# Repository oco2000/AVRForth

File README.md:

# AVRForth
Forth language compiler for AVR microcontrollers

The documentation is in [here](manual/manual.en.md)!

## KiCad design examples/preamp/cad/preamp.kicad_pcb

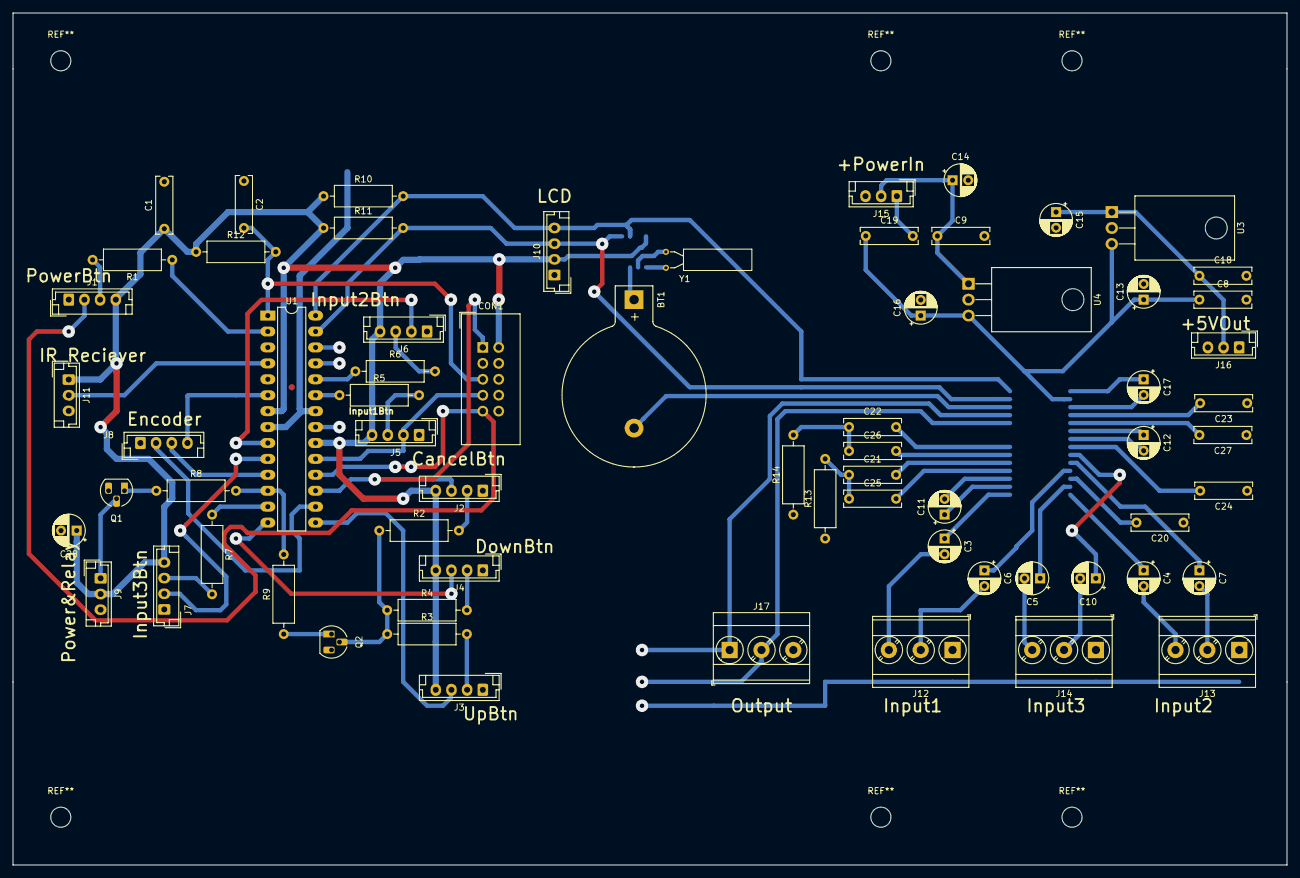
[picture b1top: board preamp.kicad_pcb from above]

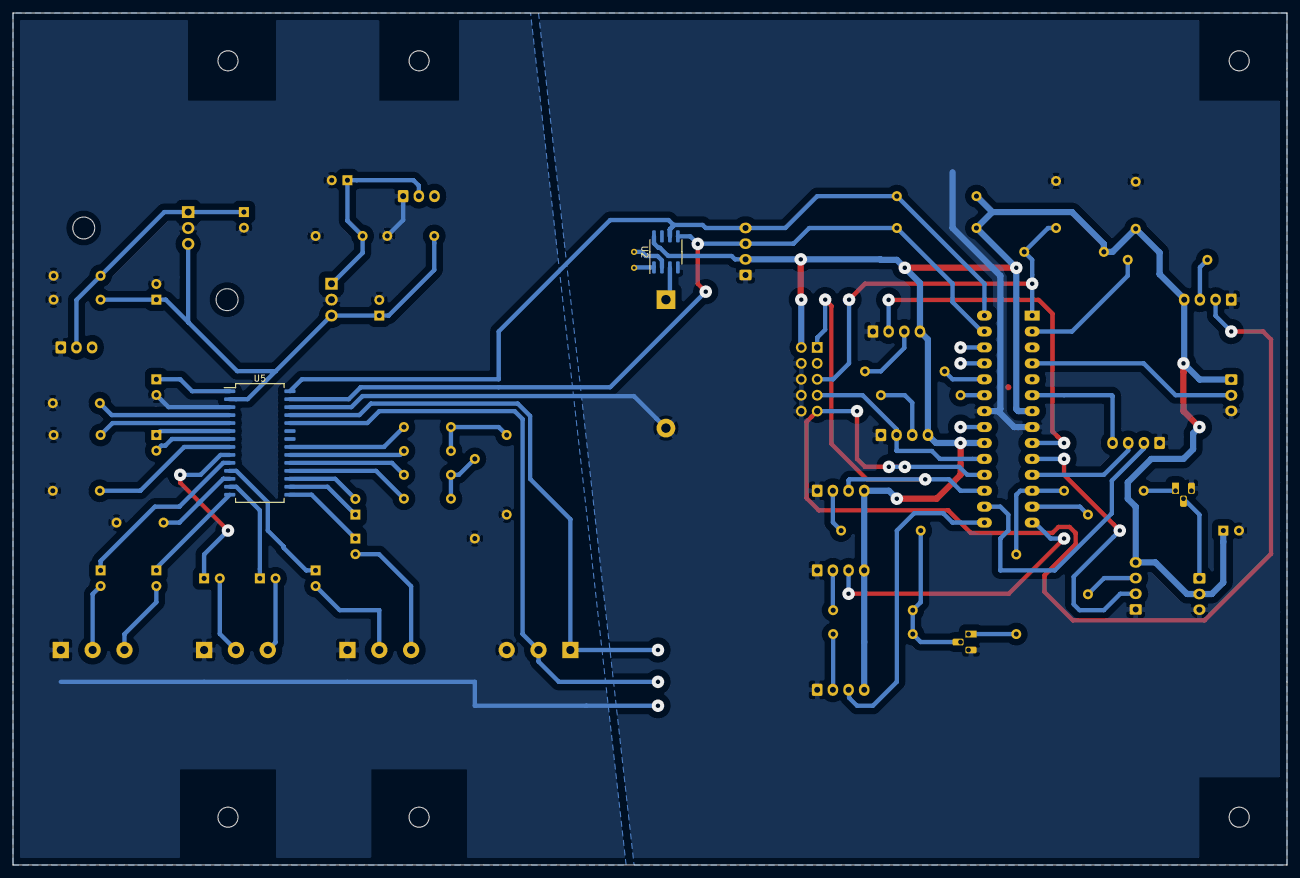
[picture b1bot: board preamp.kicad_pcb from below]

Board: 2 copper layers, 203.2 x 135.9 mm, 69 parts (2 on the bottom side), 68 nets.

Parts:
BT1: Battery_Cell; BatteryHolder_Keystone_103_1x20mm
C1, C2, C18, C19, C20, C21, C22, C24, C25, C26: 100nF; C_Rect_L9.0mm_W2.5mm_P7.50mm_MKT
C3, C4, C5, C6, C7, C10, C11, C12, C17: 2.2uF; CP_Radial_D5.0mm_P2.50mm
C8, C9: 0.33uF; C_Rect_L9.0mm_W2.5mm_P7.50mm_MKT
C13, C14, C15, C16, C28: 100uF; CP_Radial_D5.0mm_P2.50mm
C23, C27: 2.7nF; C_Rect_L9.0mm_W2.5mm_P7.50mm_MKT
CON1: AVR-ISP-10; IDC-Header_2x05_P2.54mm_Vertical
J1, J2, J3, J4, J5, J6, J7, J8, J10: Conn_01x04; JST_EH_B4B-EH-A_1x04_P2.50mm_Vertical
J9: Conn_01x03; JST_EH_B3B-EH-A_1x03_P2.50mm_Vertical
J11, J15, J16: CONN_01X03; JST_EH_B3B-EH-A_1x03_P2.50mm_Vertical
J12, J13, J14: Conn_01x03; TerminalBlock_Phoenix_MKDS-3-3-5.08_1x03_P5.08mm_Horizontal
J17: CONN_01X03; TerminalBlock_Phoenix_MKDS-3-3-5.08_1x03_P5.08mm_Horizontal
Q1, Q2: .; TO-92_HandSolder
R1, R2, R3, R4, R5, R6, R7: 1k; R_Axial_DIN0309_L9.0mm_D3.2mm_P12.70mm_Horizontal
R8, R10, R11, R12: 10k; R_Axial_DIN0309_L9.0mm_D3.2mm_P12.70mm_Horizontal
R9: 47k; R_Axial_DIN0309_L9.0mm_D3.2mm_P12.70mm_Horizontal
R13, R14: 5.6k; R_Axial_DIN0309_L9.0mm_D3.2mm_P12.70mm_Horizontal
U1: ATMEGA8A-PU; DIP-28_W7.62mm_LongPads
U2: DS1307+; SOIC-8_3.9x4.9mm_P1.27mm
U3: LM7805; TO-220-3_Horizontal_TabDown
U4: LM7809CT; TO-220-3_Horizontal_TabDown
U5: TDA7313; SOIC-28W_7.5x18.7mm_P1.27mm
Y1: Crystal; Crystal_AT310_D3.0mm_L10.0mm_Horizontal

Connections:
/+9V: C8.1, C13.1, C16.1, C19.1, U3.3, U4.3, U5.2
/BTN0: J4.3, U1.14
/BTN1: J3.3, U1.15
/BTN2: J8.2, U1.16
/BTN3_MOSI: CON1.1, J2.3, U1.17
/ENC0: J8.4, U1.6
/ENC1: J8.3, U1.11
/IRint: J11.2, U1.4
/Input1BTN_SCK: CON1.7, J5.2, U1.19
/Input1Led: R5.1, U1.23
/Input2Btn: J6.2, U1.9
/Input2Led: R6.1, U1.24
/Input3Btn: J7.2, U1.10
/Input3Led: R7.1, U1.13
/LEFT: J17.1, U1.25, U5.25
/Power: R8.2, R9.2, U1.12
/PowerBTN_MISO: CON1.9, J1.2, U1.18
/PowerLEDGND: Q2.2, R2.1, R3.1, R4.1
/RIGHT: J17.2, U1.26, U5.24
/Reset: C2.2, CON1.5, R12.2, U1.1
/SCL: J10.4, R10.2, U1.28, U2.6, U5.28
/SDA: J10.3, R11.2, U1.27, U2.5, U5.27
/StandBy: R1.1, U1.2
GND: BT1.2, C1.2, C2.1, C28.2, CON1.4, CON1.6, CON1.8, CON1.10, J1.1, J2.1, J3.1, J4.1, J5.1, J6.1, J7.1, J8.1, J9.3, J10.1, J11.3, Q1.3, Q2.3, U1.8, U1.22, U2.4, U5.26
GNDA: C8.2, C9.2, C13.2, C14.2, C15.2, C16.2, C17.2, C18.2, C19.2, C20.1, C23.1, C24.1, C27.1, J12.1, J13.1, J14.1, J15.1, J16.1, J17.3, R13.1, R14.1, U1.21, U3.2, U4.2, U5.3
unnamed: BT1.1, U2.3
unnamed: C3.1, U5.15
unnamed: C3.2, J12.3
unnamed: C4.1, U5.14
unnamed: C4.2, J13.3
unnamed: C5.1, U5.13
unnamed: C5.2, J14.3
unnamed: C6.1, U5.11
unnamed: C6.2, J12.2
unnamed: C7.1, U5.10
unnamed: C7.2, J13.2
unnamed: C10.1, U5.9
unnamed: C10.2, J14.2
unnamed: C11.1, U5.16
unnamed: C11.2, U5.17
unnamed: C12.1, U5.6
unnamed: C12.2, U5.7
unnamed: C9.1, C14.1, J15.2, U4.1
unnamed: C15.1, C18.1, J16.2, U3.1
unnamed: C17.1, U5.1
unnamed: C20.2, U5.12
unnamed: C21.1, C25.1, R13.2
unnamed: C21.2, U5.19
unnamed: C22.1, C26.1, R14.2
unnamed: C22.2, U5.21
unnamed: C23.2, U5.4
unnamed: C24.2, U5.8
unnamed: C25.2, U5.18
unnamed: C26.2, U5.20
unnamed: C27.2, U5.5
unnamed: J1.3, R1.2
unnamed: J2.2, R2.2
unnamed: J3.2, R3.2
unnamed: J4.2, R4.2
unnamed: J5.3, R5.2
unnamed: J6.3, R6.2
unnamed: J7.3, R7.2
unnamed: J9.1, Q1.2
unnamed: Q1.1, R8.1
unnamed: Q2.1, R9.1
unnamed: U2.1, Y1.1
unnamed: U2.2, Y1.2
VCC: C1.1, C28.1, CON1.2, J1.4, J2.4, J3.4, J4.4, J5.4, J6.4, J7.4, J9.2, J10.2, J11.1, R10.1, R11.1, R12.1, U1.7, U1.20, U2.8

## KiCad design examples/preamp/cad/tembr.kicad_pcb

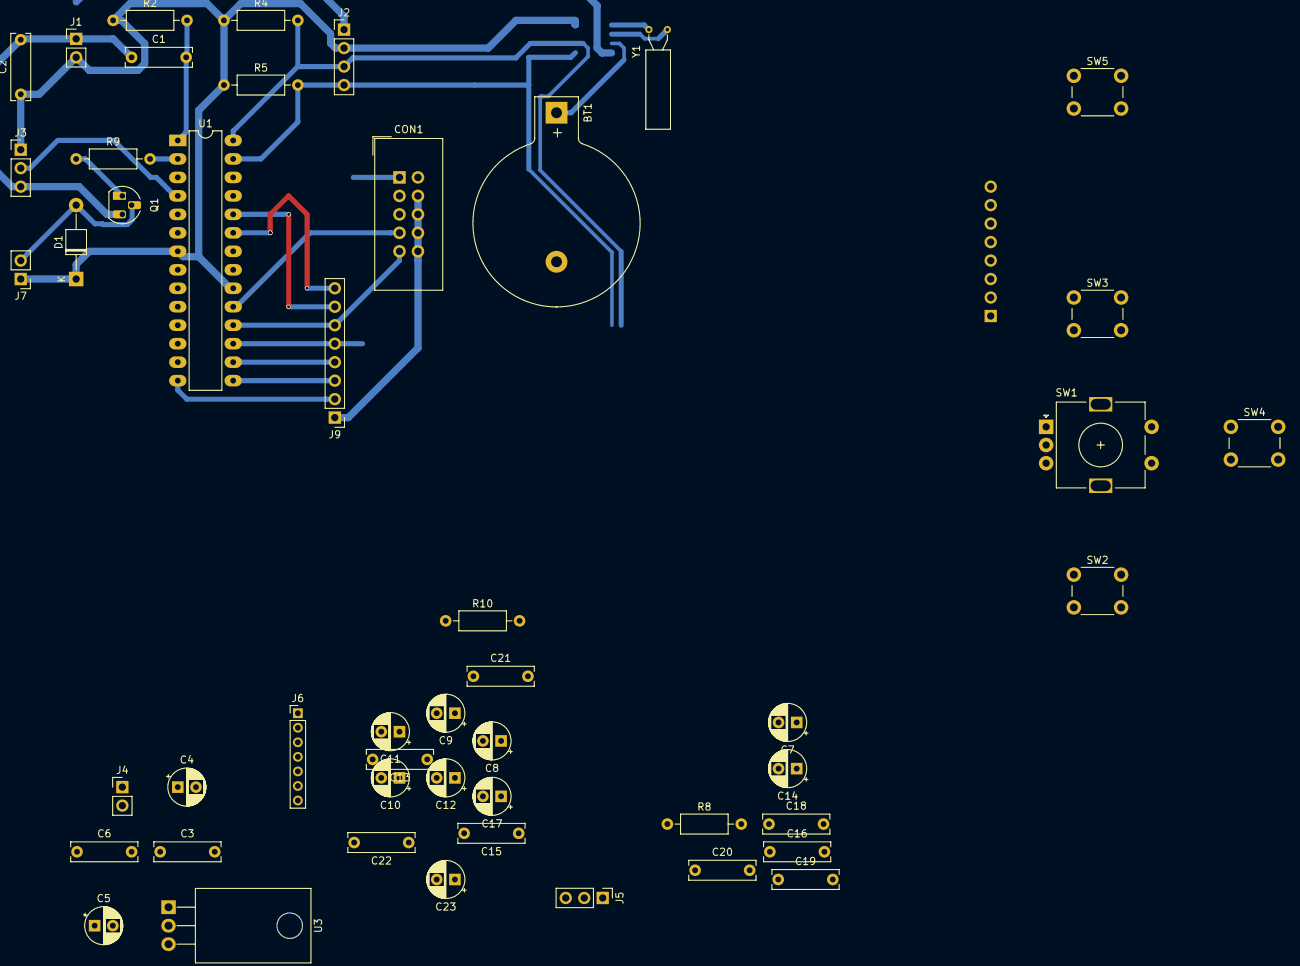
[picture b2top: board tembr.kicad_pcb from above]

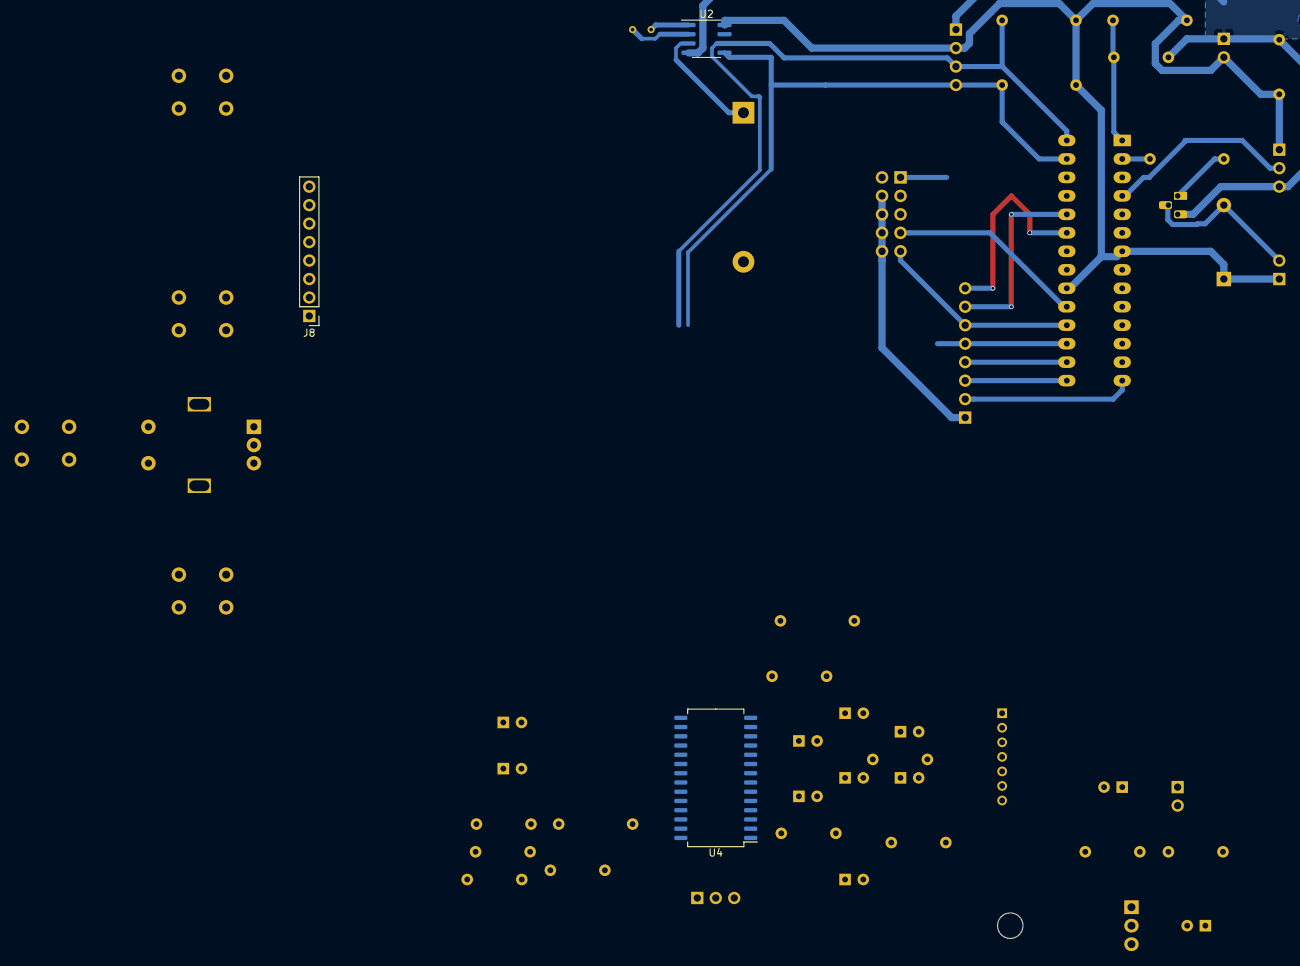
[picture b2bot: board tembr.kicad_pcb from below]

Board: 2 copper layers, 52 parts (3 on the bottom side), 60 nets.

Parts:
BT1: Battery_Cell; BatteryHolder_Keystone_103_1x20mm
C1, C2, C6, C13, C15, C16, C18, C19, C20: 100nF; C_Rect_L9.0mm_W2.5mm_P7.50mm_MKT
C3: 0.33uF; C_Rect_L9.0mm_W2.5mm_P7.50mm_MKT
C4, C5: 100uF; CP_Radial_D5.0mm_P2.50mm
C7, C8, C9, C10, C11, C12, C14, C17, C23: 2.2uF; CP_Radial_D5.0mm_P2.50mm
C21, C22: 2.7nF; C_Rect_L9.0mm_W2.5mm_P7.50mm_MKT
CON1: AVR-ISP-10; IDC-Header_2x05_P2.54mm_Vertical
D1: D; D_T-1_P10.16mm_Horizontal
J1, J4, J7: CONN_01X02; PinHeader_1x02_P2.54mm_Vertical
J2: Conn_01x04; PinHeader_1x04_P2.54mm_Vertical
J3, J5: CONN_01X03; PinHeader_1x03_P2.54mm_Vertical
J6: CONN_01X07; PinHeader_1x07_P2.00mm_Vertical
J8, J9: CONN_01X08; PinHeader_1x08_P2.54mm_Vertical
Q1: .; TO-92_HandSolder
R2, R4, R5: 10k; R_Axial_DIN0207_L6.3mm_D2.5mm_P10.16mm_Horizontal
R8, R10: 5.5k; R_Axial_DIN0207_L6.3mm_D2.5mm_P10.16mm_Horizontal
R9: 3k; R_Axial_DIN0207_L6.3mm_D2.5mm_P10.16mm_Horizontal
SW1: Rotary_Encoder; RotaryEncoder_Alps_EC11E-Switch_Vertical_H20mm
SW2, SW3, SW4, SW5: SW_Push_Dual; SW_PUSH_6mm
U1: ATMEGA8A-PU; DIP-28_W7.62mm_LongPads
U2: DS1307+; SOIC-8_3.9x4.9mm_P1.27mm
U3: LM7809CT; TO-220-3_Horizontal_TabDown
U4: TDA7313; SOIC-28W_7.5x18.7mm_P1.27mm
Y1: Crystal; Crystal_AT310_D3.0mm_L10.0mm_Horizontal

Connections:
/+9V: C5.1, C6.1, U3.3, U4.2
/A1_GND: J8.1, SW1.C, SW1.S1, SW2.1, SW3.1, SW4.1, SW5.1
/BTN0: J9.2, U1.14
/BTN1: J9.3, U1.15
/BTN2: J9.4, U1.16
/BTN3_MOSI: CON1.1, J9.5, U1.17
/ENC0: J9.8, U1.23
/ENC1: J9.7, U1.24
/IRint: J3.2, U1.4
/LEFT: J5.1, U4.25
/Power: R9.2, U1.2
/PowerBTN_MISO: CON1.9, J9.6, U1.18
/RIGHT: J5.2, U4.24
/Reset: C1.2, CON1.5, R2.2, U1.1
/SCK: CON1.7, U1.19
/SCL: J2.3, R4.2, U1.28, U2.6, U4.28
/SDA: J2.4, R5.2, U1.27, U2.5, U4.27
GND: BT1.2, C1.1, C2.2, CON1.4, CON1.6, CON1.8, CON1.10, J1.1, J2.1, J3.3, J9.1, Q1.3, U1.8, U1.22, U2.4, U4.26
GNDA: C3.2, C4.2, C5.2, C6.2, C13.1, C15.1, C21.1, C22.1, C23.2, J4.1, J5.3, J6.1, R8.1, R10.1, U1.21, U3.2, U4.3
unnamed: BT1.1, U2.3
unnamed: C3.1, C4.1, J4.2, U3.1
unnamed: C7.1, U4.15
unnamed: C7.2, J6.7
unnamed: C8.1, U4.11
unnamed: C8.2, J6.6
unnamed: C9.1, U4.14
unnamed: C9.2, J6.5
unnamed: C10.1, U4.10
unnamed: C10.2, J6.4
unnamed: C11.1, U4.13
unnamed: C11.2, J6.3
unnamed: C12.1, U4.9
unnamed: C12.2, J6.2
unnamed: C13.2, U4.12
unnamed: C14.1, U4.16
unnamed: C14.2, U4.17
unnamed: C15.2, U4.8
unnamed: C16.1, C18.1, R8.2
unnamed: C16.2, U4.19
unnamed: C17.1, U4.6
unnamed: C17.2, U4.7
unnamed: C18.2, U4.18
unnamed: C19.1, C20.1, R10.2
unnamed: C19.2, U4.21
unnamed: C20.2, U4.20
unnamed: C21.2, U4.4
unnamed: C22.2, U4.5
unnamed: C23.1, U4.1
unnamed: D1.2, J7.2, Q1.2
unnamed: J8.2, SW2.2
unnamed: J8.3, SW3.2
unnamed: J8.4, SW4.2
unnamed: J8.5, SW5.2
unnamed: J8.6, SW1.S2
unnamed: J8.7, SW1.B
unnamed: J8.8, SW1.A
unnamed: Q1.1, R9.1
unnamed: U2.1, Y1.1
unnamed: U2.2, Y1.2
VCC: C2.1, CON1.2, D1.1, J1.2, J2.2, J3.1, J7.1, R2.1, R4.1, R5.1, U1.7, U1.20, U2.8

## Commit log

2019-10-03 AVRForth moved to separate repo
2019-10-03 Create LICENSE
2019-10-03 Remove .geany file, modify changelog
2019-10-03 Start int editor
2019-10-15 AVRForth: Int editor for LCD Menu
2019-10-16 AVRForth: Int editor working
2019-10-16 AVRForth: Int editor fix negative values and refactoring
2019-10-16 AVRForth: Int editor - show string values
2019-10-17 AVRForth: Full menu and DS1307
2019-10-17 AVRForth: Fix RelJump in disassembler
2019-10-17 AVRForth: Improve listing
2019-10-17 AVRForth: Enter, exit menu
2019-10-21 Include Interrupts in listing
2019-10-21 Make MAIN mandatory
2019-10-22 Add eeprom to makefile
2019-10-23 EEPROM flashing tested
2019-10-23 Fix DS1307 access in menu test
2019-10-23 Encoder example started
2019-10-24 Encoder library and demo
2019-10-25 Encoder in menu
2019-10-30 Manual in markdown format
2019-10-31 Manual update
2019-11-01 Encoder library and demo update
2019-11-06 LCD Menu fixes
2019-11-07 Update documentation
2019-11-07 LCD Menu: Change volume from idle screen
2019-11-07 LCD Menu: Auto-close editor
2019-11-07 RC5 library started
2019-11-08 LCD I2C Connection
2019-11-08 Fix slow SPI speed
2019-11-11 RC5 library draft
2019-11-12 RC5 decoding works
2019-11-12 RC5 frequency fix
2019-11-13 RC5 code cleanup
2019-11-13 Fix Include interrupt handlers in listing
2019-11-13 Some refactoring
2019-11-13 Some cleanup and listing fix
2019-11-13 Fix Addressing bug for Mega128
2019-11-13 Version bump
2019-11-13 Changelog update
2019-11-14 LCD I2C fixes
2019-11-14 I2C Detect started
2019-11-15 I2C Detector
2019-11-16 Refactor EERTOS configuration
2019-11-16 Refactor Buttons configuration
2019-11-16 Refactor USART configuration
2019-11-16 Add BASE@ and BASE!
2019-11-16 Preamp project
2019-11-16 Version 1.5.1
2019-11-17 Preamp schematic update kicad version
2019-11-18 Start preamp PCB
2019-11-19 Rename kicad project
2019-11-19 Preamp firmware and schematic fixes
2019-11-21 Buttons library with Buses
2019-11-22 Memory bit operations
2019-11-22 Refactor buttons and LCD libs
2019-11-25 Optimize lpm instruction
2019-11-25 Optimize i2c library
2019-11-25 Optimize i2c library fix
2019-11-25 Optimize LCD menu
2019-11-25 Add TDA7313 library
2019-11-26 New ~AND word
2019-11-26 TDA7313 continued
2019-11-27 TDA7313 finished
2019-11-27 Update kicad project
2019-11-28 Preamp info display
2019-11-28 Preamp RC5 command recognition
2019-12-08 Update preamp scheme
2019-12-24 Add 3 Input buttons
2019-12-24 Code cleanup
2019-12-30 Opimize DUP>R
2020-01-08 Update preamp scheme: add led resistors
2020-01-10 Update preamp scheme: add +5V power
2020-01-13 Update preamp pcb
2020-02-19 Preamp PCB update
2020-03-10 Preamp Some fixes
2020-05-21 Fix RC5 and encoder issues
2020-05-26 Try to fix encoder crash
2020-06-04 preamp: fix encoder crash
2020-06-05 preamp: change remote, avrforth: fix disassembler crash
2020-06-06 menu: fix int editor value, preamp: set 1 input by default
2020-06-06 preamp: dont mute/unmute in sleep mode
2020-06-06 preamp: handle RC5 repeats
2020-06-06 preamp: optimizations
2020-06-08 eertos: optimize timer interrupt
2020-06-08 rc5: replace DO LOOP with BEGIN UNTIL
2020-06-08 optimize TYPE and TYPEP
2020-06-11 implement memory checks
2020-06-11 optimize EERTOS loops
2020-06-11 preamp: optimize tda7313 code
2020-06-25 preamp: fix R value
2021-09-23 update spf
2023-10-13 Preamp example KiCAD upgrade
2024-09-06 v1.5.6
2024-09-09 Stepper library and example
2024-09-09 I2C Detect with UART
2024-09-09 RTC with UART
2024-09-09 Hall sensor test
2024-09-09 v1.5.7
2024-09-13 Flap clock example started, some fixes
2024-09-27 Flap clock example, UART receiver
2024-10-07 English translation
2024-10-07 English translation finished
2024-10-11 Bluetooth example
2024-10-29 Flap clock example, more UART commands
2026-05-08 Clock update to reboot if RTC is not detected
